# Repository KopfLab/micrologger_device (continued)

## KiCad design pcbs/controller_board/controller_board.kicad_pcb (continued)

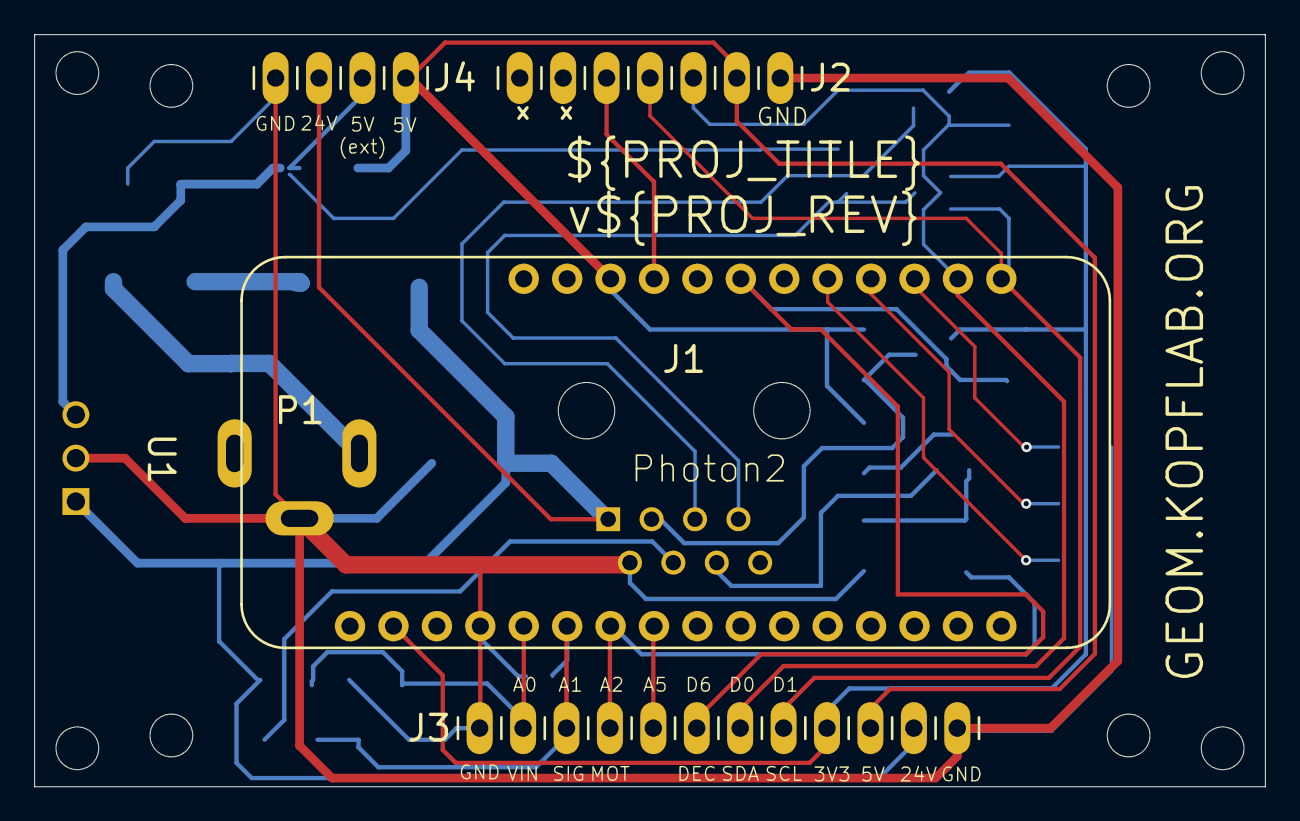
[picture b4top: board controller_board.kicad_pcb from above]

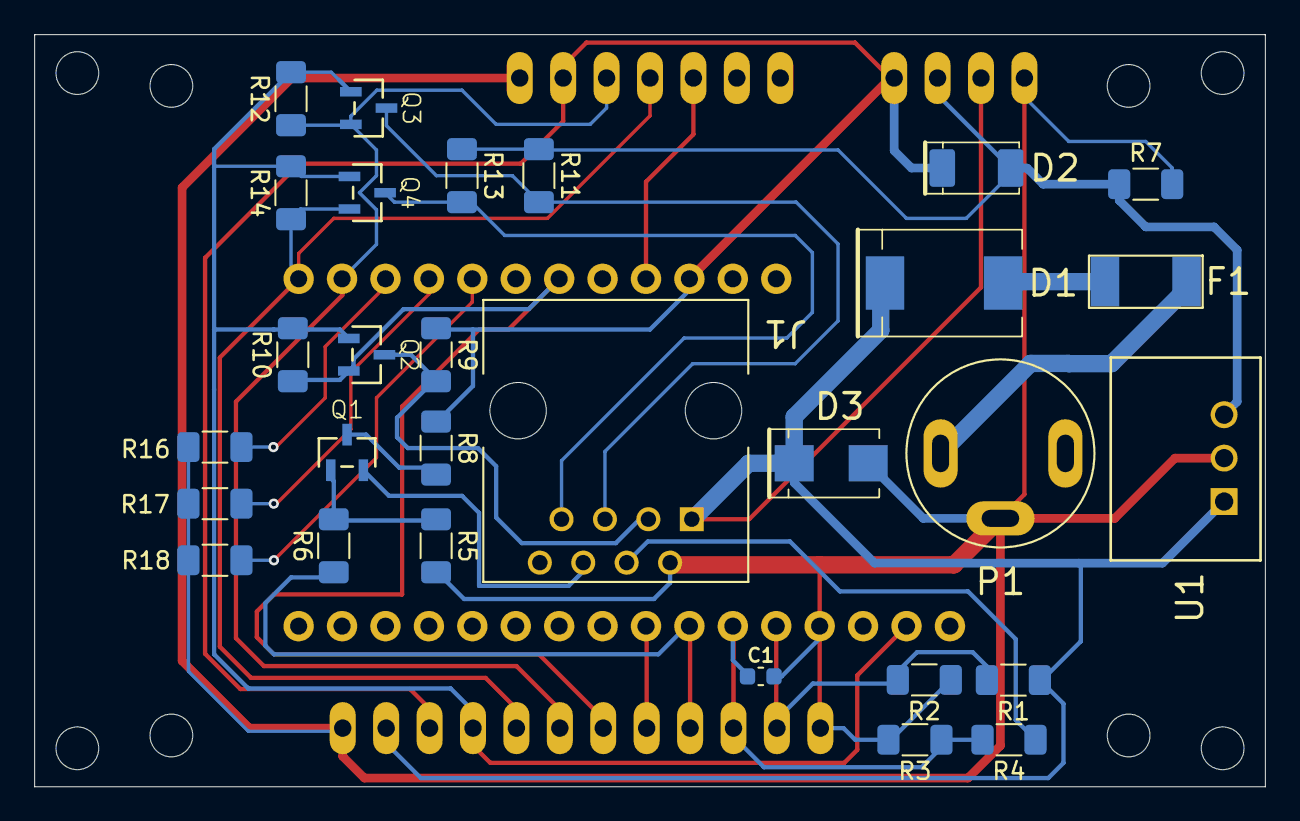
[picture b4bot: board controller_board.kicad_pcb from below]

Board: 2 copper layers, 72.0 x 44.0 mm, 41 parts (29 on the bottom side), 25 nets.

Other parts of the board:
H1, H2, H3, H4, H5, H6, H7, H8: MountingHole_2.5mm_M2.5

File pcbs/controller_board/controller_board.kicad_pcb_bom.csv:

Designator,Quantity,Value,Footprint,Package,MPN,DNP,Mount_Type,Description,JLCPCB,JLCPCBURL,FP_Status,DigiKey,DigiKeyURL,UnitPrice,ParticleURL
C1,1,10nF,C_0603,,,,smt,Unpolarized capacitor,C1589,https://jlcpcb.com/partdetail/1941-CL10B103KB8NNNC/C1589,,,,,
D1,1,3A/60V/750mV,D_DO-214AB_SMC,,SS36,,tht,Diode 60 V 3A Surface Mount DO-214AB (SMC),C391251,https://jlcpcb.com/partdetail/onsemi-SS36/C391251,done,SS36FSCT-ND,https://www.digikey.com/en/products/detail/onsemi/SS36/1053019,,
D2,1,1A/40V/500mV,D_DO-214AC_SMA,,SS14,,smt,Diode 40 V 1A Surface Mount DO-214AC (SMA),C83852,https://jlcpcb.com/partdetail/onsemi-SS14/C83852,done,SS14CT-ND,https://www.digikey.com/en/products/detail/onsemi/SS14/965474,,
D3,1,40V,D_DO-214AA_SMB,,SMBJ36A,,tht,58.1V Clamp 10.4A Ipp Tvs Diode Surface Mount DO-214AA (SMBJ),C224020,https://jlcpcb.com/partdetail/Littelfuse-SMBJ36A/C224020,done,SMBJ36ALFCT-ND,https://www.digikey.com/en/products/detail/littelfuse-inc/SM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,,
F1,1,33V/750mA/1.5A,Fuse_1812,,MF-MSMF075/33X-2,,smt,Polymeric PTC Resettable Fuse 33V 750 mA Ih Surface Mount 1812,C3760814,https://jlcpcb.com/partdetail/BOURNS-MF_MSMF075_33X2/C3760814,done,118-MF-MSMF075/33X-2CT-ND,https://www.digikey.com/en/products/detail/bourns-inc/MF-MSM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,0.91,
J1,1,RJ45,RJ45_A-2014-2-4-N-T-R,,A-2014-2-4-N-T-R,,tht,"Jack Modular Connector 8p8c (RJ45, Ethernet) Vertical Unshielded",,,done,AE10396-ND,https://www.digikey.com/en/products/detail/assmann-wsw-compo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,,
J2,1,Conn_01x07,PIN_HEADERS_1X07,,,,tht,"Basic 0.1"" PTH",,,done,,,,
J3,1,Conn_01x12,PIN_HEADERS_1X12,,,,tht,"Basic 0.1"" PTH",,,done,,,,
J4,1,PINHD-1X4,PIN_HEADERS_1X04,,,,tht,"Basic 0.1"" PTH",,,done,,,,
P1,1,24V / 5A,PWR_JACK_PJ-064A,,PJ-064A,,tht,"2.0 mm Center Pin, 5.0 A, Vertical, Panel Mount, PC Pins, Dc Power Jack Connector",,,done,CP-064A-ND,https://www.digikey.com/en/products/detail/cui-devices/PJ-06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,,
"Q1, Q2, Q3, Q4",4,220mA / 50V,SOT-23-3,,BSS138,,tht,N-Channel 50 V 2200mA 350mW (Ta) Surface Mount SOT-23-3,C52895,https://jlcpcb.com/partdetail/onsemi-BSS138/C52895,done,BSS138CT-ND,https://www.digikey.com/en/products/detail/onsemi/BSS138/244210,,
R1,1,150kΩ,R_1206,,,,smt,"Resistor, US symbol",C17916,https://jlcpcb.com/partdetail/18604-1206W4F1503T5E/C17916,done,,,,
"R10, R11, R12, R13, R14, R16, R17, R18, R2, R5, R7, R9",12,10kΩ,R_1206,,,,smt,"Resistor, US symbol",C17902,https://jlcpcb.com/partdetail/18590-1206W4F1002T5E/C17902,done,,,,
R3,1,100kΩ,R_1206,,,,smt,"Resistor, US symbol",C17900,https://jlcpcb.com/partdetail/18588-1206W4F1003T5E/C17900,done,,,,
"R4, R8",2,1kΩ,R_1206,,,,smt,"Resistor, US symbol",C4410,https://jlcpcb.com/partdetail/4817-1206W4F1001T5E/C4410,done,,,,
R6,1,150Ω,R_1206,,,,smt,"Resistor, US symbol",C17917,https://jlcpcb.com/partdetail/18605-1206W4F1500T5E/C17917,done,,,,
U1,1,8-28V in / 5V 5W out,DC_DC_converter_R-78E5.0-1.0,,R-78E5.0-1.0,,tht,Linear Regulator Replacement DC DC Converter 1 Output 5V 1A 8V - 28V Input,,,done,945-2201-ND,https://www.digikey.com/en/products/detail/recom-power/R-78E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,,
U2,1,Particle2 / Boron,PHOTON2,,PHN2MEA / BRN404,,tht,Particle Photon 2 Wi-Fi enabled development kit,,,done,,,,https://store.particle.io/collections/wifi/products/photon-2

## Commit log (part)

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2025-03-14 start gitignore
2025-03-14 readme and license
2025-03-14 add available commands
2025-03-14 add makefile
2025-03-14 add blinking test
2025-03-14 add i2c scanner
2025-03-14 basic logger controller
2025-03-14 update formatting
2025-07-16 setup rake and guard infrastructure
2025-07-16 ignore local files
2025-07-16 scad and stl files
2025-07-16 pcb boards
2025-07-16 add SDDS submodules
2025-07-16 deprecated with move to SDDS
2025-07-16 move programs to tests
2025-07-16 make local folder work more automatically
2025-07-16 add blink test
2025-07-16 setup micrologger files
2025-07-16 add draft micrlogger class
2025-07-16 update watch paths
2025-07-16 update docs for guard
2025-07-17 update rake file
2025-07-17 implement stirrer sdds framework
2025-07-17 beam start
2025-07-23 move hardware commands to separate class
2025-07-30 revise hardware initailization and error reporting
2025-07-30 update publish namespace and publish errors immediately
2025-07-31 simplify without event checks
    based on new SDDS changed info in reactive events
2025-08-27 upgrade to SDDS v0.1.0
    simplify the enumerations access
2025-11-13 kicad files for led board
2025-11-13 update gitignore for pcbs
2025-11-14 controller board in kicad
2025-11-14 update gitignore
2025-11-14 small updates and BOM
2025-11-15 cleanup footprints and symbols
2025-11-15 relocate libraries
2025-11-15 add footprint status to parts
2025-11-15 update symbol and footpring libraries
2025-11-15 fix label positioning
2025-11-16 fix current for fuse
2025-11-23 fix orientation of text labels
2025-12-09 fix size of drill holes for power jack
2025-12-09 add capacitors and I2C level shifter parts
2025-12-09 update controller board to v0.80
    - switch 5V rail to go to device (instead of light output)
    - improve protection of 3V/5V I2C bus by using an IC instead of mosfets
    - bleed resistor from external 5V to gnd to avoid floating voltage
2025-12-09 simplify guard
2025-12-09 remove dependency on guardrc
2025-12-09 implement 'rake dev PROGRAM' properly
2025-12-12 v 0.81 (removed the 5V on the RJ45)
2025-12-13 i2C hardware bse class
2025-12-13 TCA9534 IO expander (via i2c) hardware class
2025-12-13 i2c connect always checks the connection now
2025-12-13 include board version information (version 1.0)
2025-12-15 update symbols and add additoinal footprints
2025-12-15 update sensor board
2025-12-15 lock controller board parts
2025-12-15 update part info
2025-12-15 include background for board picture
2025-12-15 update bom list
2025-12-15 fix red LED part
2025-12-15 sensor board version 1.1
2025-12-18 add SDDS controller for Nidec24H motor
2025-12-24 implement fine-adjustment based on speed measurement
2025-12-24 motor test program
2025-12-24 add github submodules for oled
2025-12-27 update controller board to version 1.1 - i2c level shifting back to mosfets
2025-12-27 add BusIO submodules for OLED
2025-12-27 update rake targets (firmware check & library flexibility)
2026-01-07 implemented improved I2C base class and IOexpander
2026-01-07 add busio submodule
2026-01-09 clean up i2c classes --> private vs protected functions
2026-01-09 draft for i2c pwm dimmer
2026-01-09 write and read on auto (re)connect
2026-01-09 finalize v1 of pwm dimmer
2026-01-12 add hardware components
2026-01-12 add lights menu class
2026-01-15 temperature sensor board
2026-01-15 project libraries
2026-01-15 add single pin header and temperature sensor chip to footprints/symbols libraru
2026-01-16 restructure submodule
2026-01-16 restructure submodules
2026-01-16 add BusIO submodule in the correct place
2026-01-16 repos cleanup
2026-01-16 submodule cleanup
2026-01-16 recorgnize sub modules
2026-01-16 add splash screen
2026-01-16 draft of oled base class
2026-01-19 introduce reset action for i2c device base class
2026-01-19 first draft of display ssd display class
2026-01-19 add pragma once for splash
2026-01-19 add information symbols
2026-01-19 add publishig symbols
2026-01-19 update pwm speed contorl
2026-01-19 update symbol spacing
2026-01-20 add version information
2026-01-20 add separate core enmerations
2026-01-21 implement auto-resume for motor reconnection
2026-01-22 second draft of full light control
2026-01-22 update enumerations
2026-01-22 update to latest particlespike
2026-01-22 remove unused code
2026-01-22 units update
2026-01-22 add units to stirrer
2026-01-22 include units
2026-01-22 correct units (lower case)
2026-01-22 but hardware pins and addresses into constants
2026-01-22 update hardware to include dimmer
2026-01-22 update units and fix HHMM configuration
2026-01-22 micrologger with stirrer and lights control
2026-01-22 make display details persistant (via saveval
2026-01-22 switch hardware to be not in spike intervals but still in menu
2026-01-22 introduce lights event
2026-01-22 rename stirevent to just event for clarity
2026-01-22 deal with pause properly
2026-01-23 upgrade to version 1.2
    - lower resistor for indicator LEDs (brighter)
    - better position for indicator LEDs (left/right)
    - io expander beam/indicator LED switched (=backwards compatibility)
    - switch contacts for the fan (opposite to the lights)
2026-01-24 update symbols and footprints
2026-01-24 use updated header symbols, otherwise no changes
2026-01-24 sensor board version 1.3
2026-01-24 add rheostats
2026-01-24 auto-write on startup
2026-01-24 fix capacitor placaement on sensor board (IN- to SIGNAL)
2026-01-29 add signal stabilizing capacitors to controller and sensor boards
2026-01-29 add digital potentiometers
2026-01-29 only update sdds vars if they have changed
2026-01-29 remove error message
2026-01-29 implement gain and signal informatio into optical density
2026-01-29 incorporate draft of optical density
2026-01-30 update expander to write pin modes before reading values (same as for writing values)
2026-01-30 implement pcb version recognition
2026-01-30 move opt signal to its own hardware class
2026-01-30 make motor hardware class more specific
2026-01-30 reorganize component files for clarity
2026-01-30 categorize display correctly
2026-01-30 correct reference to hardwaredisplay
2026-01-30 restructure class names towards "component" prefix
2026-01-30 implement automatic gain adjustment
2026-01-30 remove overly verbose log messages
2026-01-30 make sure pin definitions happen in the hardware (caused issues with motor)
2026-01-31 vortex and stirrer control in optical density module added
2026-02-02 add temperature sensor in environment component
2026-02-02 add code for input voltage sensing
2026-02-02 add voltage and temperature reporting
2026-02-02 implemented placeholder puase state function
2026-02-03 update version to have major and minor options
2026-02-03 have sensor be active/passive options
2026-02-03 complete draft of optical density reader
2026-02-05 sensor board version 1.4
2026-02-05 controller board version 1.2 (just the signal cap added)
2026-02-05 update led board to version 1.0 (just text upates)
2026-02-05 version 1.0 of the temperature sensor
2026-02-06 fix automatic stirring adjusment to be less volatile and deal well with missed decoder interrupts
    basically using a gated system now and the upper 25% percentile of histogram data
2026-02-06 deal correctly with starting nans for floats
2026-02-06 fix resume to work correctly for optical density readings
2026-02-06 update information display on oled
2026-02-06 make sure sensor state resumes last and fix bug in optical density reading at low stir rates
2026-02-06 allow for 3 point version
2026-02-06 clean up hardware (mcp4652 and mlx90614 removed)
2026-02-06 make splashscreen required (just time can be changed)
2026-02-06 save all motor settings
2026-02-06 introduce units for acceleration/decelleration
2026-02-06 switch temperature read interval to ms (although with I2C it probably can't go faster than 500ms)
2026-02-06 read interval form sec to ms and signal reads stay as specified in the hardware
2026-02-25 add dependencies for stl models
2026-02-25 cleanup stl generation code
2026-02-28 make base adapter notches longer and cleanup code
2026-02-28 add adpater for hungate tube
2026-02-28 add new stl models
2026-02-28 add adapters readme
2026-02-28 add pngs for stl models
2026-02-28 update 3D printed pngs
2026-02-28 update listing of 3d parts
2026-02-28 fix sorting
2026-03-02 make base adapter hooks longer
2026-03-06 optimize printing for fewer travels (with 8 wall print)
2026-03-06 make base adapters screw attachable
2026-04-04 add units
2026-04-04 update variable names and units
2026-04-09 upadte sdds particlespike submodule
2026-04-09 add next publishing information to display
2026-04-09 change publishing defaults
2026-04-09 fully implement zero waiting period
2026-04-09 update particle spike library
2026-04-09 simplify version
2026-04-10 version 1.4.1 - includes proper snapshot handling
2026-04-14 implement mode based signal averaging
2026-04-19 implement getSddsPublish
2026-04-19 make sure that time intervals are uint32
2026-04-19 update particle spike to latest version
2026-04-19 introduce setting to decide whether to pause lights or not
2026-04-20 add about section
2026-04-20 use latest particlespike
2026-04-20 introduce NEWS
2026-04-20 rename publishing.publish to publishing.record
2026-04-20 clarify controller is designed for 0.5mm nozzle
2026-04-20 add custom prints and increase beam block depth to 7.5mm to accomodate a wider range of LEDs
2026-04-20 release version 1.5
2026-04-23 specify data event for more specialized webhook
2026-05-02 add kicad history to gitignore
2026-05-02 update LED board with multiple resistor options
2026-05-02 update I2C info
2026-05-02 update LED board with multiple resistors and jumper
2026-05-02 update sensor board with 1M potentiometer
2026-05-29 update particle spike
